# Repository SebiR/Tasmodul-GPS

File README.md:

# Tasmodul GPS
A module to get live GPS coordinates into MQTT with Tasmota or other home automation systems

## Features
* SMA connector for external GPS antenna
* Micro USB for powering and data access

## Notes
* The battery (ML414H_IV01E) can be ordered on AliExpress, that's probably the easiest way
* Tasmota does not include GPS capability by default. It has to be compiled with custom parameters to include it

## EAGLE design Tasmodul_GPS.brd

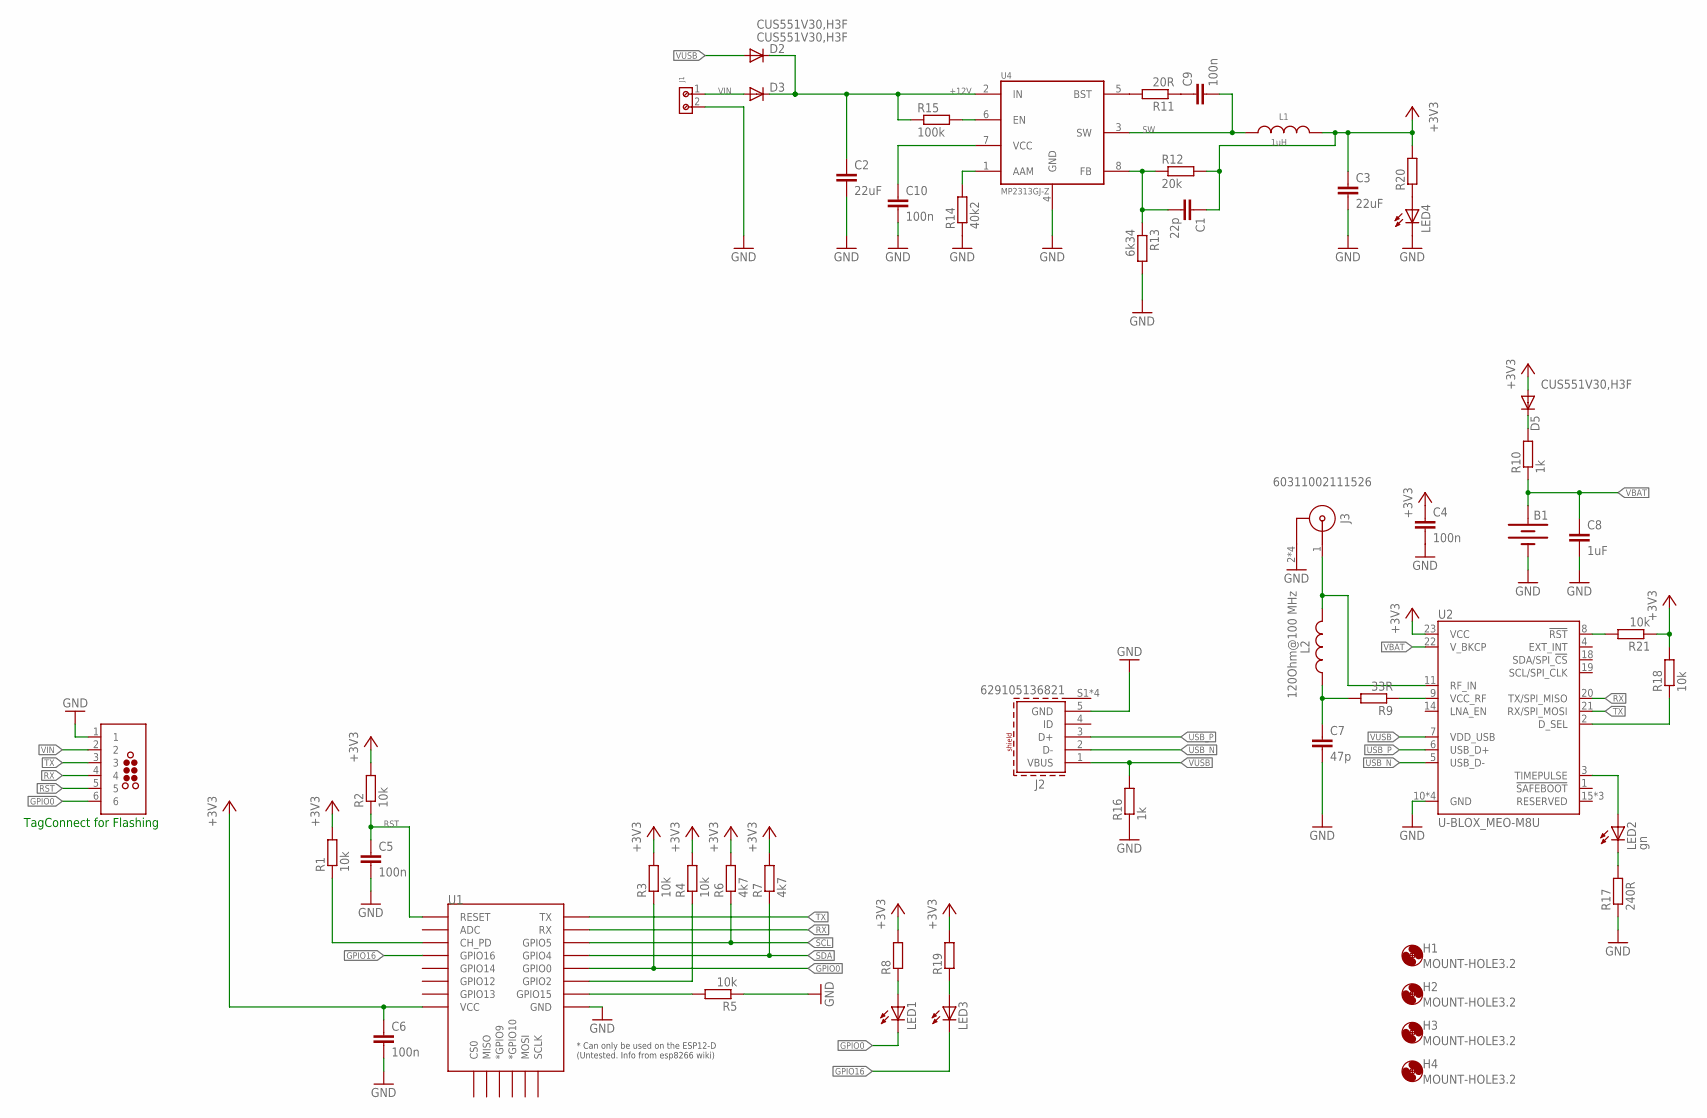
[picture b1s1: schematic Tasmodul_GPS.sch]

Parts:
B1: 6.8MM_COIN_CELL; ML414H_IV01E
C1: 22p; C0603
C2, C3: 22uF; C0805
C4, C5, C6, C9, C10: 100n; C0603
C7: 47p; C0603
C8: 1uF; C0603
D2, D3, D5: CUS551V30,H3F; SOD323-R
H1, H2, H3, H4: MOUNT-HOLE3.2; 3,2
J1: 691210910002
J2: 629105136821
J3: 60311002111526
J6: TC2030-MCP-NL
L1: 1uH; WE-TPC_2811_OLD
L2: 120Ohm@100 MHz; WE-CBF_0603(W=2.2)
LED1, LED3, LED4: LEDCHIP-LED0603; CHIP-LED0603
LED2: gn; CHIP-LED0603
R1, R2, R3, R4, R5, R18, R21: 10k; R0603
R6, R7: 4k7; R0603
R8, R19, R20: R-EU_R0603; R0603
R9: 33R; R0603
R10, R16: 1k; R0603
R11: 20R; R0603
R12: 20k; R0603
R13: 6k34; R0603
R14: 40k2; R0603
R15: 100k; R0603
R17: 240R; R0603
U1: ESP12ESMD; ESP12E-SMD
U2: U-BLOX_MEO-M8U; NEO-M9N/M8T/M8U
U4: MP2313GJ-Z; TSOT23-8_MPS

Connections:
+3V3: C1.1, C3.1, C4.1, C6.1, D5.A, L1.2, R1.2, R2.2, R3.2, R4.2, R6.2, R7.2, R8.2, R12.2, R18.2, R19.2, R20.2, R21.1, U1.VCC, U2.23 (VCC)
+12V: C2.1, D2.C, D3.C, R15.1, U4.2 (IN)
GND: B1.-, C2.2, C3.2, C4.2, C5.2, C6.2, C7.2, C8.2, C10.2, J1.2, J2.5 (GND), J3.2, J3.3 (2), J3.4 (2), J3.5 (2), J6.1, LED4.C, R5.1, R13.2, R14.1, R16.1, R17.1, U1.GND, U2.10 (GND), U2.12 (GND), U2.13 (GND), U2.24 (GND), U4.4 (GND)
GPIO0: J6.6, LED1.C, R3.1, U1.GPIO0
GPIO16: LED3.C, U1.GPIO16
unnamed: LED1.A, R8.1
unnamed: LED2.C, R17.2
unnamed: J3.1, L2.2, U2.11 (RF_IN)
unnamed: R21.2, U2.8 (!RST)
unnamed: R1.1, U1.CH_PD
unnamed: R5.2, U1.GPIO15
unnamed: R4.1, U1.GPIO2
unnamed: D5.C, R10.2
unnamed: R11.2, U4.5 (BST)
unnamed: C9.1, R11.1
unnamed: R9.1, U2.9 (VCC_RF)
unnamed: C1.2, R12.1, R13.1, U4.8 (FB)
unnamed: C10.1, U4.7 (VCC)
unnamed: R14.2, U4.1 (AAM)
unnamed: R15.2, U4.6 (EN)
unnamed: C7.1, L2.1, R9.2
unnamed: LED2.A, U2.3 (TIMEPULSE)
unnamed: R18.1, U2.2 (D_SEL)
unnamed: LED3.A, R19.1
unnamed: LED4.A, R20.1
RST: C5.1, J6.5, R2.1, U1.RESET
RX: J6.4, U1.RXD0 (RX), U2.20 (TX/SPI_MISO)
SCL: R6.1, U1.GPIO5
SDA: R7.1, U1.GPIO4
SW: C9.2, L1.1, U4.3 (SW)
TX: J6.3, U1.TXD0 (TX), U2.21 (RX/SPI_MOSI)
USB_N: J2.2 (D-), U2.5 (USB_D-)
USB_P: J2.3 (D+), U2.6 (USB_D+)
VBAT: B1.+, C8.1, R10.1, U2.22 (V_BKCP)
VIN: D3.A, J1.1, J6.2
VUSB: D2.A, J2.1 (VBUS), R16.2, U2.7 (VDD_USB)

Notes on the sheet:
TagConnect for Flashing

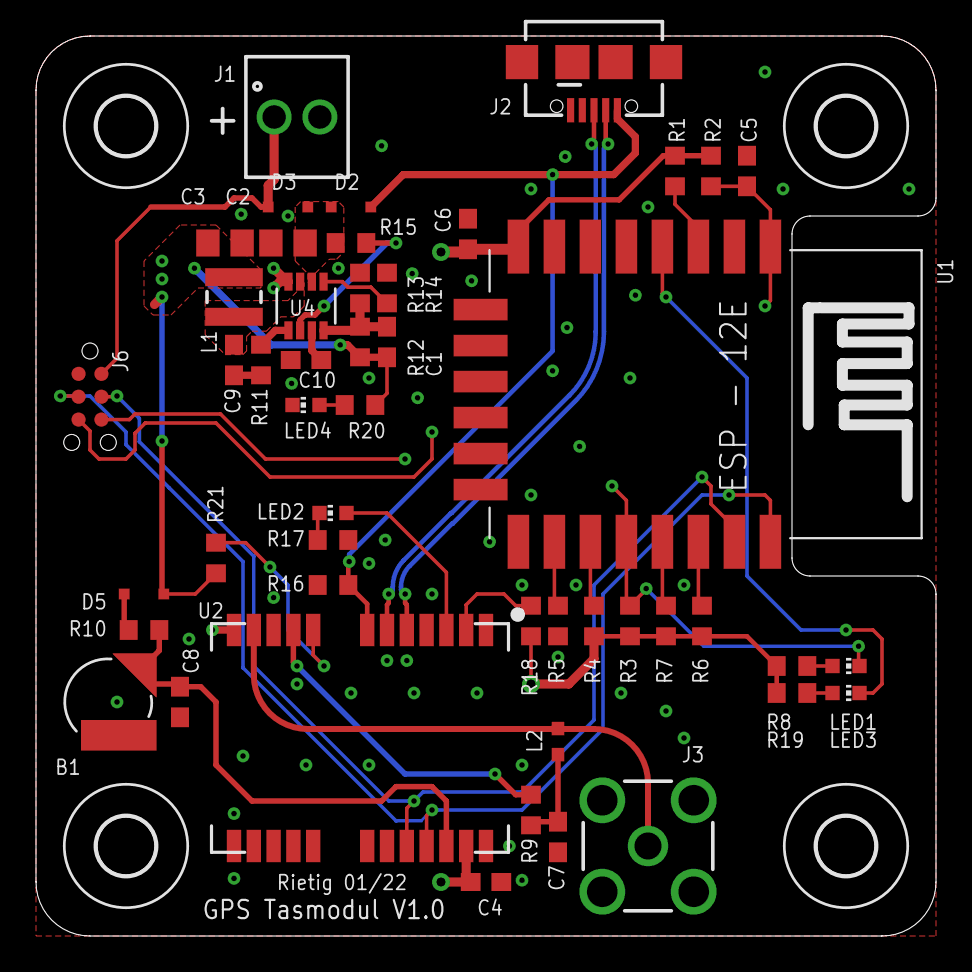
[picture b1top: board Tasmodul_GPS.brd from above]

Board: 4 copper layers, 50.0 x 50.0 mm, 52 parts (0 on the bottom side), 36 nets.

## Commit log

2023-04-22 Changed picture

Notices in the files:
parts and their libraries:
Eagle_WR-TBL Rising Cage Clamp: Copyright: Würth Elektronik
SparkFun-GPS: Licensing: Creative Commons ShareAlike 4.0 International - https://creativecommons.org/licenses/by-sa/4.0
tag-connect: ©2009 ROFA.cz - modified and updated by Robert Darlington ‹rdarlington@gmail.com›
